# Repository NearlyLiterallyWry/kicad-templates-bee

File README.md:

kicad-templates-bee
===================

This repository contains KiCad project templates for [bees](https://github.com/beecourse).

For info on templates see the [official documentation](http://docs.kicad-pcb.org/master/en/kicad/kicad.html#project_templates).

Installation
------------
Clone this repository to a directory of your choice. Open KiCad and go to _Preferences_ > _Configure Paths_. Replace the path in KICAD_USER_TEMPLATE_DIR with the previously chosen directory.

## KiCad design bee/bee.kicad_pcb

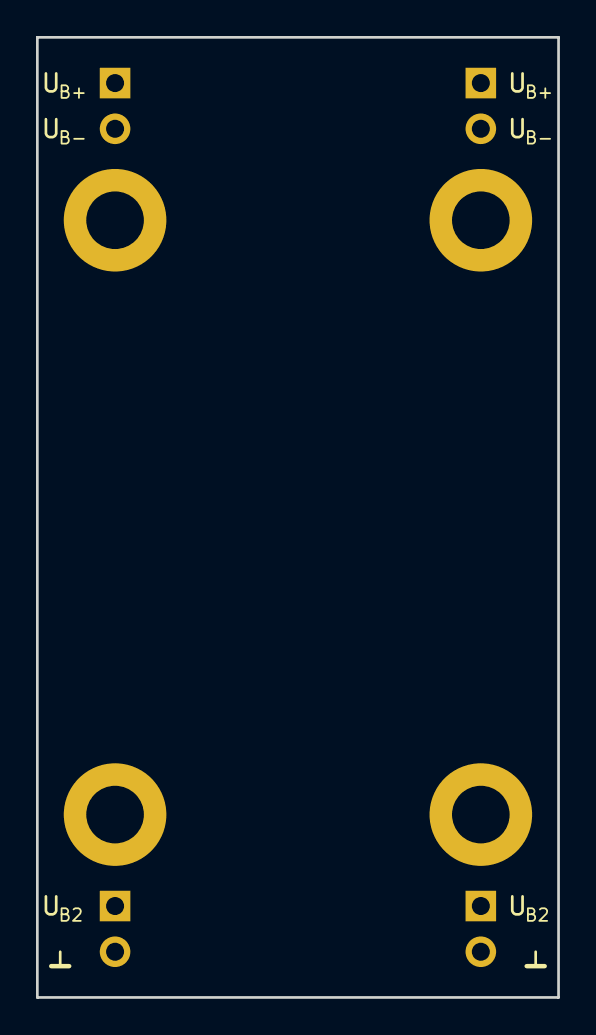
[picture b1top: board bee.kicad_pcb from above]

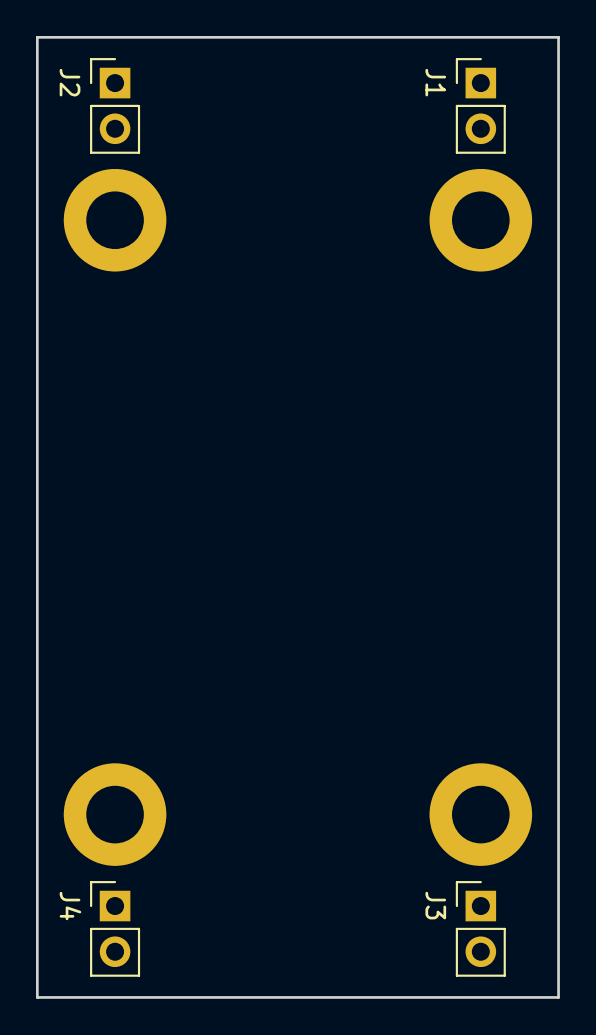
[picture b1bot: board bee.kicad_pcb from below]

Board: 2 copper layers, 29.0 x 53.3 mm, 16 parts (4 on the bottom side), 4 nets, no tracks yet.

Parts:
H1, H2: Silkscreen_Label; Text_U_B+_Silkscreen
H3, H4: Silkscreen_Label; Text_U_B-_Silkscreen
H5, H6: Silkscreen_Label; Text_U_B2_Silkscreen
H7, H8: Silkscreen_Label; Symbol_GND_Silkscreen
H9, H10, H11, H12: MountingHole_Pad; MountingHole_3.2mm_M3_ISO7380_Pad
J1, J2, J3, J4: Conn_01x02_Male; PinHeader_1x02_P2.54mm_Vertical

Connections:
+5V: J3.1, J4.1
+15V: J1.1, J2.1
-15V: J1.2, J2.2
GND: H9.1, H10.1, H11.1, H12.1, J3.2, J4.2

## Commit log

2019-02-26 Add readme.
2019-02-26 Add gitignore.
2019-02-26 Add breadboard expansion board template.
2019-02-26 Add breadboard expansion board with half width.
2019-02-26 Describe installation.
2019-02-26 Lock mounting holes.
2019-04-09 Add voltage labels.
2019-04-15 Increase PCB width of base format.
2019-04-15 Increase width of half base format.
2019-04-15 Update gitignore. Remove *.net-files.
2019-04-15 Rename breadboard_expansion to bee.
2019-04-15 Rename half width bee.
2019-04-29 Add sch symbols for labels, update PCB accordingly.
2019-04-29 Replace vias by mounting holes.
2019-04-29 Hide mounting hole reference on silkscreen.
2019-04-29 Move gitignore to templates.
    This automatically includes the gitignore in new projects.
2019-05-10 Add part numbers.
2020-07-01 Relabel as bee specific.
2020-07-03 Translate menu items in README.md-file.
2020-07-15 Add license.
